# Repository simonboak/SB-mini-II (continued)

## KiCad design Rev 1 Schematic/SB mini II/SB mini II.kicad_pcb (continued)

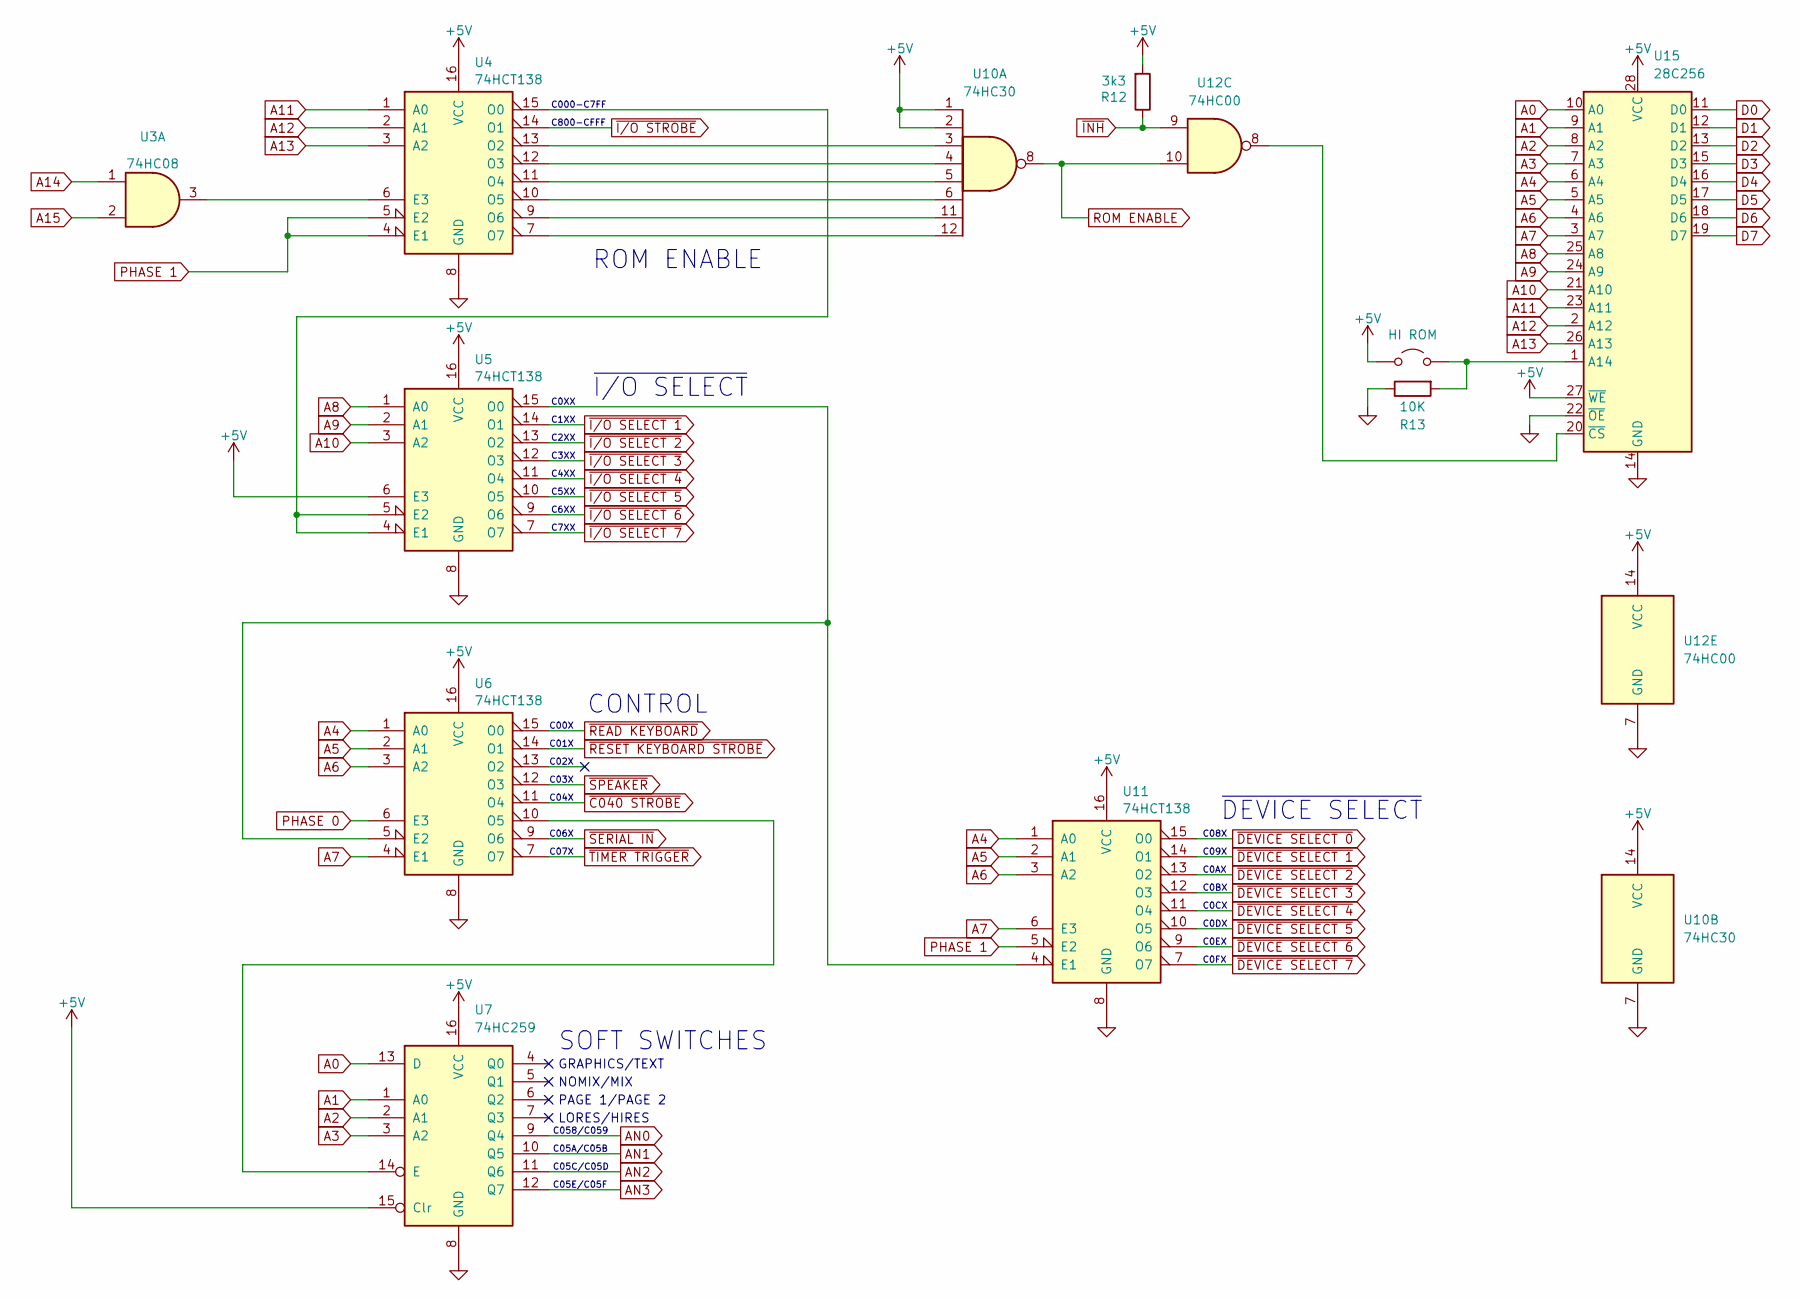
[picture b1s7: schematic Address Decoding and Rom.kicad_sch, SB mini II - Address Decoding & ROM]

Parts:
JP1: HI ROM; TestPoint_2Pads_Pitch2.54mm_Drill0.8mm
R12: 3k3; R_Axial_DIN0207_L6.3mm_D2.5mm_P7.62mm_Horizontal
R13: 10K; R_Axial_DIN0207_L6.3mm_D2.5mm_P7.62mm_Horizontal
U3: 74HC08; DIP-14_W7.62mm_LongPads
U4, U5, U6, U11: 74HCT138; DIP-16_W7.62mm_LongPads
U7: 74HC259; DIP-16_W7.62mm_LongPads
U10: 74HC30; DIP-14_W7.62mm_LongPads
U12: 74HC00; DIP-14_W7.62mm_LongPads
U15: 28C256; DIP-28_W15.24mm_LongPads

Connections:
+5V: JP1.1 (A), R12.2, U4.16 (VCC), U5.6 (E3), U5.16 (VCC), U6.16 (VCC), U7.15 (Clr), U7.16 (VCC), U10.1, U10.2, U10.14 (VCC), U11.16 (VCC), U12.14 (VCC), U15.27 (~WE), U15.28 (VCC); also elsewhere on the board
A0: U7.13 (D), U15.10 (A0); also elsewhere on the board
A1: U7.1 (A0), U15.9 (A1); also elsewhere on the board
A2: U7.2 (A1), U15.8 (A2); also elsewhere on the board
A3: U7.3 (A2), U15.7 (A3); also elsewhere on the board
A4: U6.1 (A0), U11.1 (A0), U15.6 (A4); also elsewhere on the board
A5: U6.2 (A1), U11.2 (A1), U15.5 (A5); also elsewhere on the board
A6: U6.3 (A2), U11.3 (A2), U15.4 (A6); also elsewhere on the board
A7: U6.4 (E1), U11.6 (E3), U15.3 (A7); also elsewhere on the board
A8: U5.1 (A0), U15.25 (A8); also elsewhere on the board
A9: U5.2 (A1), U15.24 (A9); also elsewhere on the board
A10: U5.3 (A2), U15.21 (A10); also elsewhere on the board
A11: U4.1 (A0), U15.23 (A11); also elsewhere on the board
A12: U4.2 (A1), U15.2 (A12); also elsewhere on the board
A13: U4.3 (A2), U15.26 (A13); also elsewhere on the board
A14: U3.1; also elsewhere on the board
A15: U3.2; also elsewhere on the board
AN0: U7.9 (Q4); also elsewhere on the board
AN1: U7.10 (Q5); also elsewhere on the board
AN2: U7.11 (Q6); also elsewhere on the board
AN3: U7.12 (Q7); also elsewhere on the board
D0: U15.11 (D0); also elsewhere on the board
D1: U15.12 (D1); also elsewhere on the board
D2: U15.13 (D2); also elsewhere on the board
D3: U15.15 (D3); also elsewhere on the board
D4: U15.16 (D4); also elsewhere on the board
D5: U15.17 (D5); also elsewhere on the board
D6: U15.18 (D6); also elsewhere on the board
D7: U15.19 (D7); also elsewhere on the board
GND: R13.1, U4.8 (GND), U5.8 (GND), U6.8 (GND), U7.8 (GND), U10.7 (GND), U11.8 (GND), U12.7 (GND), U15.14 (GND), U15.22 (~OE); also elsewhere on the board
unnamed: JP1.2 (B), R13.2, U15.1 (A14)
unnamed: U3.3, U4.6 (E3)
unnamed: U4.15 (O0), U5.4 (E1), U5.5 (E2)
unnamed: U4.13 (O2), U10.3
unnamed: U4.12 (O3), U10.4
unnamed: U4.11 (O4), U10.5
unnamed: U4.10 (O5), U10.6
unnamed: U4.9 (O6), U10.11
unnamed: U4.7 (O7), U10.12
unnamed: U6.10 (O5), U7.14 (E)
unnamed: U5.15 (O0), U6.5 (E2), U11.4 (E1)
unnamed: U12.8, U15.20 (~CS)
PHASE 0: U6.6 (E3); also elsewhere on the board
PHASE 1: U4.4 (E1), U4.5 (E2), U11.5 (E2); also elsewhere on the board
ROM ENABLE: U10.8, U12.10
~C040 STROBE: U6.11 (O4); also elsewhere on the board
~DEVICE SELECT 0: U11.15 (O0); also elsewhere on the board
~DEVICE SELECT 1: U11.14 (O1); also elsewhere on the board
~DEVICE SELECT 2: U11.13 (O2); also elsewhere on the board
~DEVICE SELECT 3: U11.12 (O3); also elsewhere on the board
~DEVICE SELECT 4: U11.11 (O4); also elsewhere on the board
~DEVICE SELECT 5: U11.10 (O5); also elsewhere on the board
~DEVICE SELECT 6: U11.9 (O6); also elsewhere on the board
~DEVICE SELECT 7: U11.7 (O7); also elsewhere on the board
~INH: R12.1, U12.9; also elsewhere on the board
~I/O SELECT 1: U5.14 (O1); also elsewhere on the board
~I/O SELECT 2: U5.13 (O2); also elsewhere on the board
~I/O SELECT 3: U5.12 (O3); also elsewhere on the board
~I/O SELECT 4: U5.11 (O4); also elsewhere on the board
~I/O SELECT 5: U5.10 (O5); also elsewhere on the board
~I/O SELECT 6: U5.9 (O6); also elsewhere on the board
~I/O SELECT 7: U5.7 (O7); also elsewhere on the board
~I/O STROBE: U4.14 (O1); also elsewhere on the board
~READ KEYBOARD: U6.15 (O0); also elsewhere on the board
~RESET KEYBOARD STROBE: U6.14 (O1); also elsewhere on the board
~SERIAL IN: U6.9 (O6); also elsewhere on the board
~SPEAKER: U6.12 (O3); also elsewhere on the board
~TIMER TRIGGER: U6.7 (O7); also elsewhere on the board

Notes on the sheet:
GRAPHICS/TEXT
C07X
C1XX
C0AX
C800-CFFF
C08X
C4XX
C000-C7FF
C05E/C05F
C0FX
C058/C059
C2XX
CONTROL
LORES/HIRES
C0XX
C09X
C0CX
C01X
~{DEVICE SELECT}
ROM ENABLE
C04X
C6XX
C06X
C05C/C05D
PAGE 1/PAGE 2
C00X
C05A/C05B
C0BX
C0DX
C0EX
NOMIX/MIX
C5XX
SOFT SWITCHES
C7XX
C03X
C3XX
~{I/O SELECT}
C02X

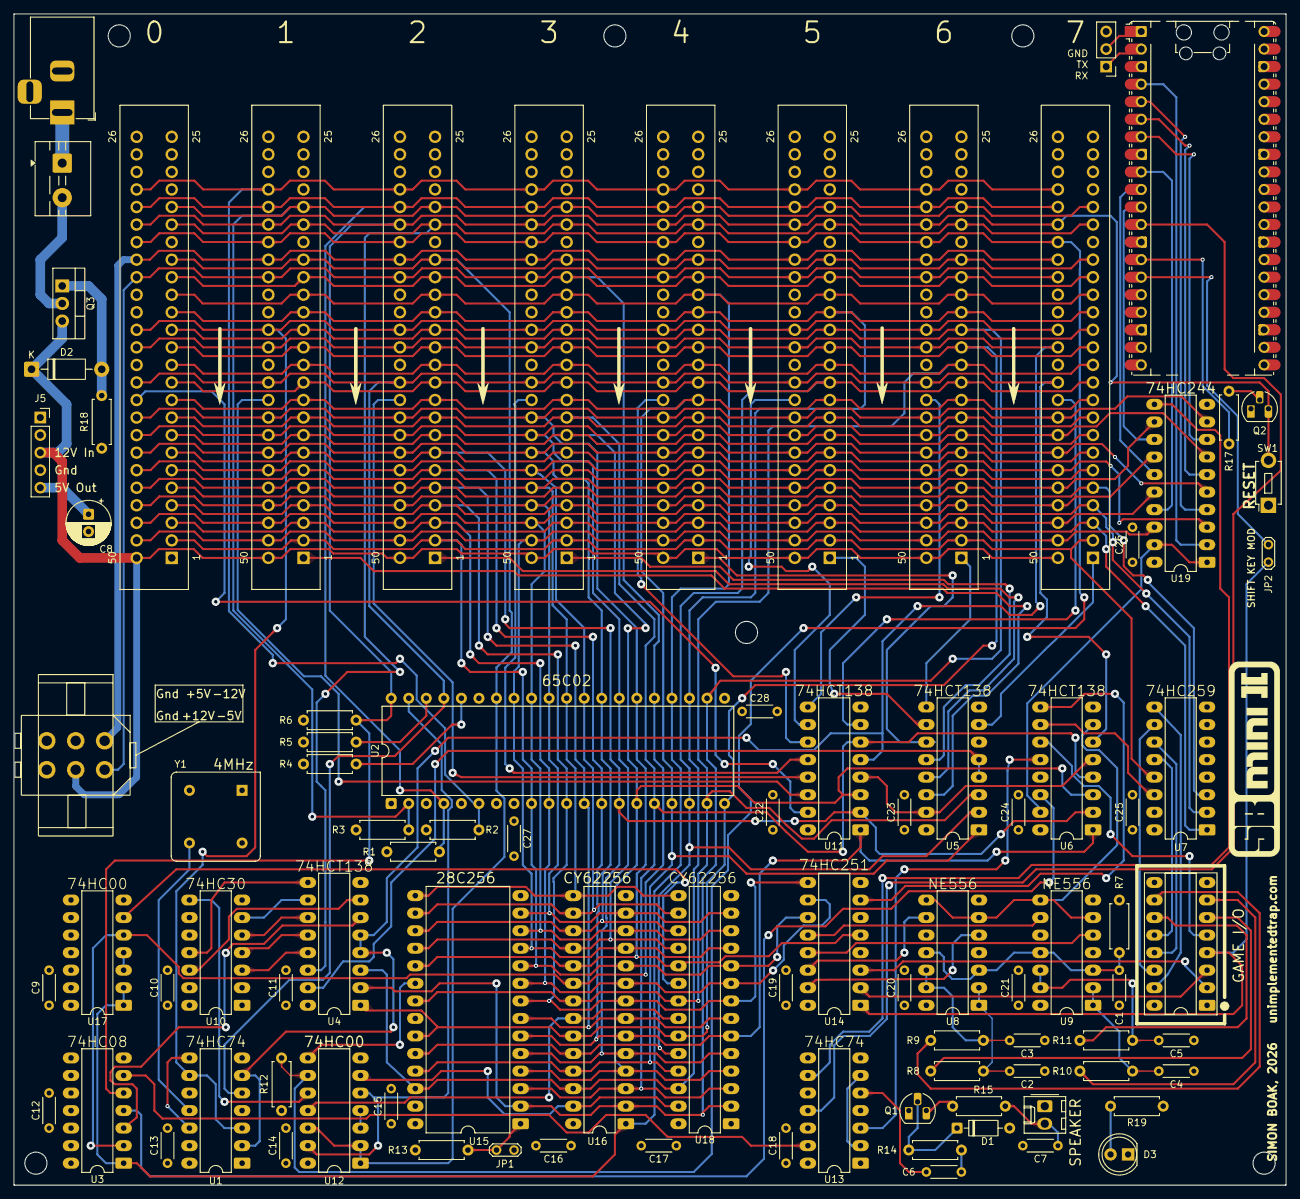
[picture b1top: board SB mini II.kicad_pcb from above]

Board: 4 copper layers, 184.2 x 169.5 mm, 97 parts (0 on the bottom side), 128 nets.

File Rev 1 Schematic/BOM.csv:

Reference,Value,Qty
A1,Raspberry Pi Pico 1,1
"C1,C6,C7,C9,C10,C11,C12,C13,C14,C15,C16,C17,C18,C19,C20,C21,C22,C23,C24,C25,C26,C27,C28,C29",0.1µF,24
"C2,C3,C4,C5",22nF,4
C8,470µF,1
D1,1N914,1
D2,1N5240B,1
D3,3 or 5mm power indicator LED,1
J1,GAME I/O: DIP-16 socket,1
J2,Pico Debug: 3 pin header,1
J3,PCB Barrel Jack,1
J4,Terminal block for power switch,1
J5,Pololu 5V 1A Step-Down Voltage Regulator (D24V10F5),1
J6,Apple II Power Connector,1
JP1,HI ROM selector: 2 pin header,1
JP2,SHIFT KEY MOD: 2 pin header,1
LS1,Speaker 20mm 0.5W,1
Q1,MPSA13,1
Q2,PN2222A,1
Q3,IRF5305,1
"R1,R2,R3,R4,R5,R12",3k3,6
"R6,R16,R17",1k,3
R7,2k5,1
"R8,R9,R10,R11",100,4
R13,10K,1
R14,47k,1
R15,27,1
R18,100k,1
R19,330,1
"Slot1,Slot2,Slot3,Slot4,Slot5,Slot6,Slot7,Slot8",50 pin card edge connector,8
SW1,RESET: MJTP/PHAP33 tactile switch ,1
"U1,U13",74HC74,2
U2,65C02,1
U3,74HC08,1
"U4,U5,U6",74HC138,3
U7,74HC259,1
"U8,U9",NE556,2
U10,74HC30,1
U11,74HCT138,1
"U12,U17",74HC00,2
U14,74HC251,1
U15,28C256 32k x 8 EEPROM,1
"U16,U18",CY62256 32k x 8 SRAM,2
U19,74HC244,1
Y1,4MHz square can crystal oscillator,1

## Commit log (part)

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2026-06-23 Initial project files
2026-06-23 Adding some readme images
2026-06-27 Adding archive of KiCad schematics
2026-06-28 Adding cutaway img
2026-06-28 Add blog post link to README
    Updated README to include a link to the blog post.
